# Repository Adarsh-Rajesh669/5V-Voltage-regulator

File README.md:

# 5V Voltage Regulator using 7805 IC
 A basic 5V voltage regulator using the 7805 linear voltage regulator IC. It converts an unregulated DC input (7V to 15V) into a stable 5V output, ideal for powering microcontrollers, sensors, and other 5V logic devices.
 
# Components Used :

7805 Voltage Regulator IC

Input Capacitor: 100 µF 

Output Capacitor: 10µF

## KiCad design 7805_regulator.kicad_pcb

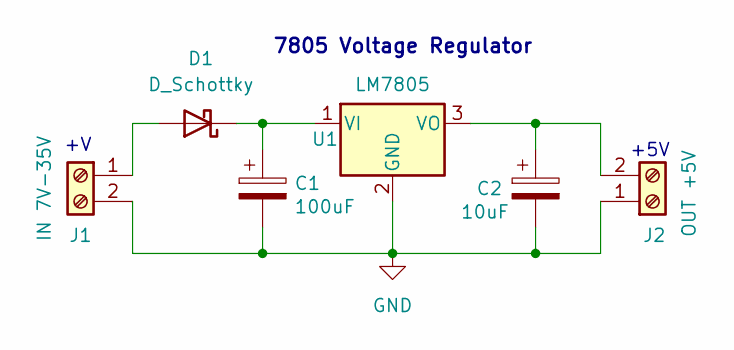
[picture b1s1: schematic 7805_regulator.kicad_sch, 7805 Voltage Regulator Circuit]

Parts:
C1: 100uF; CP_Radial_D5.0mm_P2.50mm
C2: 10uF; CP_Radial_D5.0mm_P2.50mm
D1: D_Schottky; D_0805_2012Metric
J1: IN 7V-35V; TerminalBlock_bornier-2_P5.08mm
J2: OUT +5V; TerminalBlock_bornier-2_P5.08mm
U1: LM7805; TO-220-3_Vertical

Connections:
GND: C1.2, C2.2, J1.2, J2.1, U1.2 (GND)
unnamed: D1.2 (A), J1.1
unnamed: C1.1, D1.1 (K), U1.1 (VI)
unnamed: C2.1, J2.2, U1.3 (VO)

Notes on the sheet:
7805 Voltage Regulator
+5V

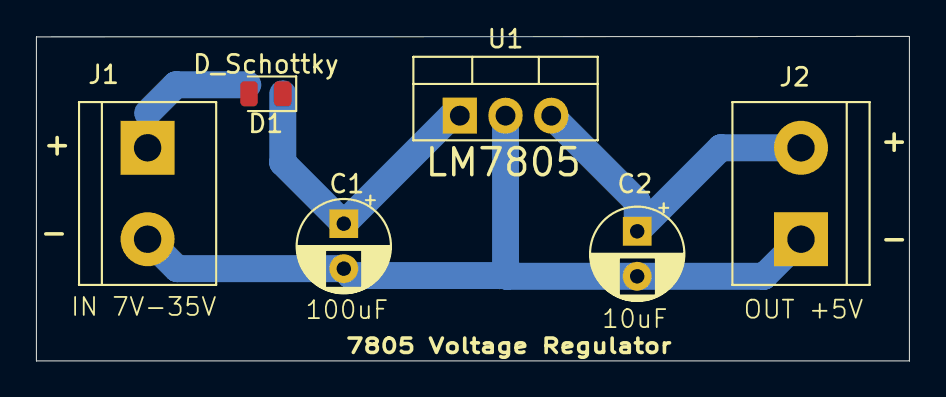
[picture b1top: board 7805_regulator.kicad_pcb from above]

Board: 2 copper layers, 48.5 x 18.0 mm, 6 parts (0 on the bottom side), 4 nets.

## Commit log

2025-06-23 Create lg
